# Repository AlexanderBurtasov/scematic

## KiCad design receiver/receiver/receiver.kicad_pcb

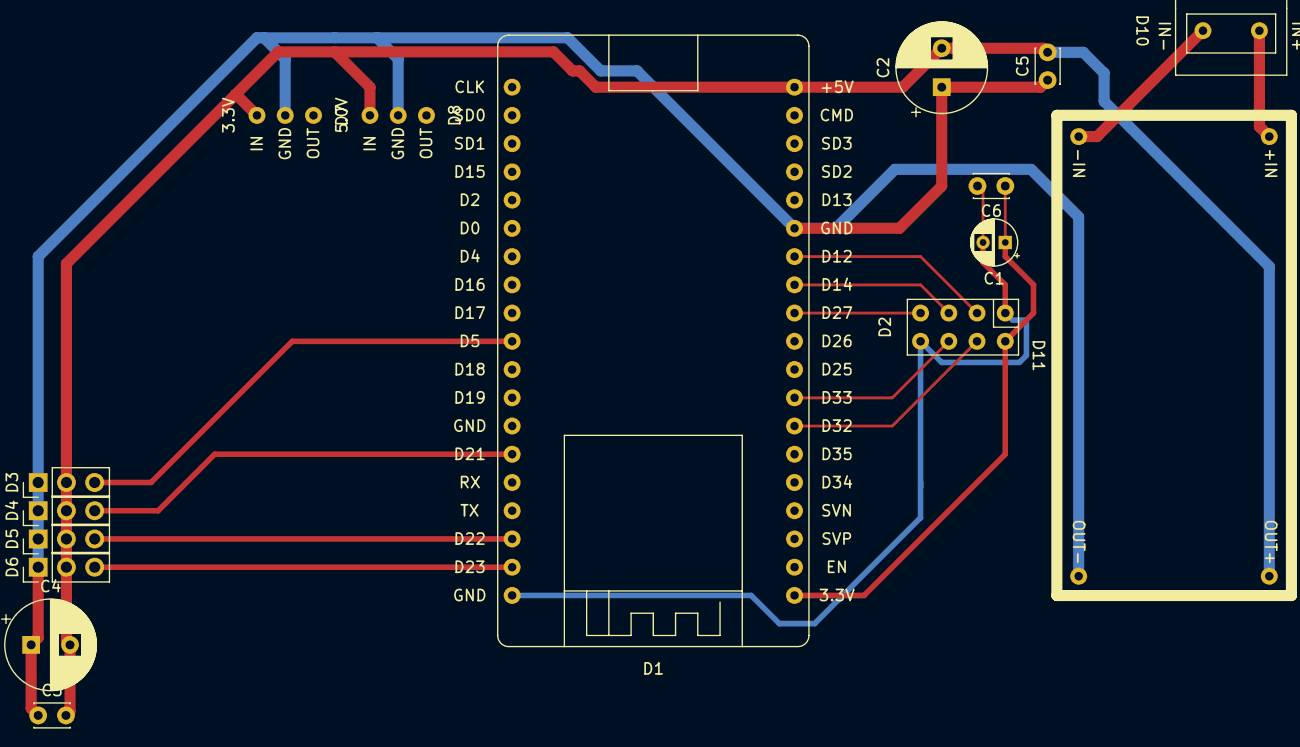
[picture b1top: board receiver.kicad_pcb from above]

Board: 2 copper layers, 16 parts (0 on the bottom side), 15 nets.

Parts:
C1: 100microF; CP_Radial_D4.0mm_P2.00mm
C2, C4: 470microF; CP_Radial_D8.0mm_P3.50mm
C3, C5, C6: 0.1microF; C_Disc_D3.0mm_W2.0mm_P2.50mm
D1: ESP32-devkit-C; esp32-devkit-C
D2: nrf24l01
D3, D4, D5, D6: servo_connector; PinHeader_1x03_P2.54mm_Vertical
D7: 3.3V; 3.3V-converter
D8: 5.0V; 5.0V-converter
D10: cleat_2pin
D11: LM2596

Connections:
+3V3: C1.1, C6.1, D1.20 (3.3V), D2.8 (3.3V)
+7.5V: C2.2, C3.2, C4.2, C5.2, D1.38 (+5V), D3.2 (VCC), D4.2 (VCC), D5.2 (VCC), D6.2 (VCC), D7.1 (IN), D8.1 (IN), D11.4 (OUT+)
+12V: D10.1 (PLUS), D11.1 (+IN)
/D5: D1.10 (D5), D3.3 (PWM)
/D21: D1.14 (D21), D4.3 (PWM)
/D22: D1.17 (D22), D5.3 (PWM)
/D23: D1.18 (D23), D6.3 (PWM)
GND: D10.2 (MINUS), D11.2 (-IN)
GND1: C2.1, C3.1, C4.1, C5.1, D1.33 (GND), D3.1 (GND), D4.1 (GND), D5.1 (GND), D6.1 (GND), D7.2 (GND), D8.2 (GND), D11.3 (OUT-)
GND2: C1.2, C6.2, D1.19 (GND), D2.1 (GND), D2.5 (IRQ)
unnamed: D1.26 (D32), D2.7 (CSN)
unnamed: D1.27 (D33), D2.6 (MOSI)
unnamed: D1.30 (D27), D2.4 (MISO)
unnamed: D1.31 (D14), D2.3 (SCK)
unnamed: D1.32 (D12), D2.2 (CE)

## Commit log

2020-07-31 add 100mF capacitor
2020-08-07 add pins
2020-08-10 LM2596
